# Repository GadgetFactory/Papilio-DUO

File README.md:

Papilio-DUO
==============

This is the next generation Papilio FPGA board with a Spartan6 Powered Papilio FPGA on the top and an atmega32u4 Arduino derived design on the bottom.

Features
--------
* Arduino Mega Footprint
* Spartan 6 FPGA
* SRAM 512K-2MB
* FT2232H USB
* atmega32u4 AVR

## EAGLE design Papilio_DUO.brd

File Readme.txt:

BPC3012 Papilio DUO Manufacturing Package - Current Version 1.7

Special assembly instructions:
	-Use RED for the PCB color and white for the silkscreen color.

Test Plan Home Page:
	- http://www.gadgetfactory.net/opmanuals/index.php?n=Main.PapilioDUO

CHANGELOG
2/11/2015 V1.7
	-Added a 2MB and 512KB marking to the top silkscreen.

1/7/2015 V1.6
	-Made the through holes for mounting on the micro-usb via's instead of holes so they can be soldered.
	-Removed Kickstarter edition
	-Fixed angles on some of the traces
	-PCB color is RED now.

9/30/2014 V1.5 - Kickstarter Edition
	-Added TQFP footprint for the ATmega32U4
	-Changed values for LED resistors so they won't be so bright. R7, R29, R30
	-Changed size of the EEPROM used by the FT2232H chip from 1K to 2K. This allows us to look like official Xilinx Cable. U3
	-Fixed up some silkscreen markings to make it more obvious how to place the parts.
	-Added the Kickstarter Special Edition Marking
	-Changed PCB color to Black

7/30/2014 V1.4
	-Added getting started URL
	-Fixed full silkscreen	

6/4/2014 V1.4
	-Fixed the mounting holes
	-Removed original Arduino mounting holes

4/16/2014 V1.3
	-VBUS connected
	-RX/TX LED's changed to port B
	-Silkscreen changes
	-HDMI removed

3/5/2014 V1.2
	-Shrunk the board to 100cm in order to better fit Chinese standards and save money in manufacturing.

3/5/2014 V1.1
	-Fixed problems for manufacturability (thanks to Mitch at Hackvana)
		-Fixed clearance problem on FPGA pins 144 and 36
		-Moved trace between FT2232H pins 10 and 11 to inside of part so it does not look like a solder bridge up on inspection.
		-Fixed Silkscreen size for the 22-53 numbering
		-Updated the CC-BY-SA text to indicate license number CC-BY-SA 4.0

3/3/2014 V1.0
	Initial Release

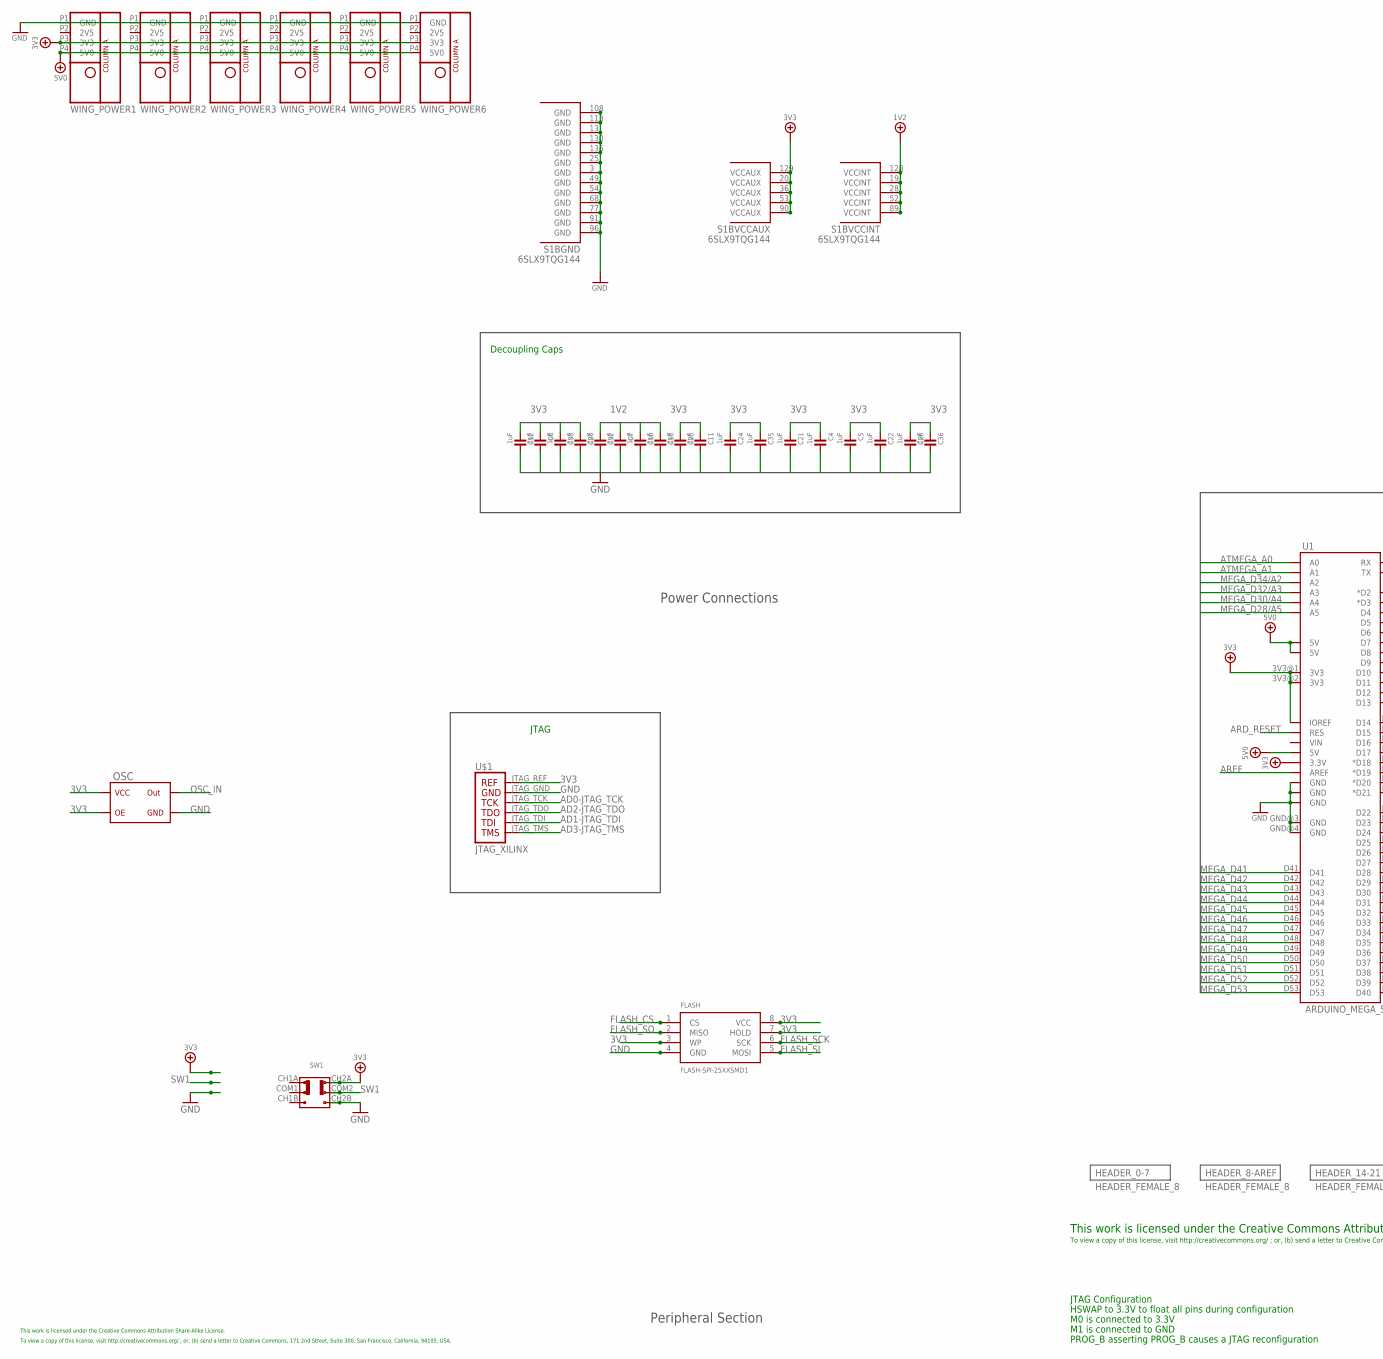
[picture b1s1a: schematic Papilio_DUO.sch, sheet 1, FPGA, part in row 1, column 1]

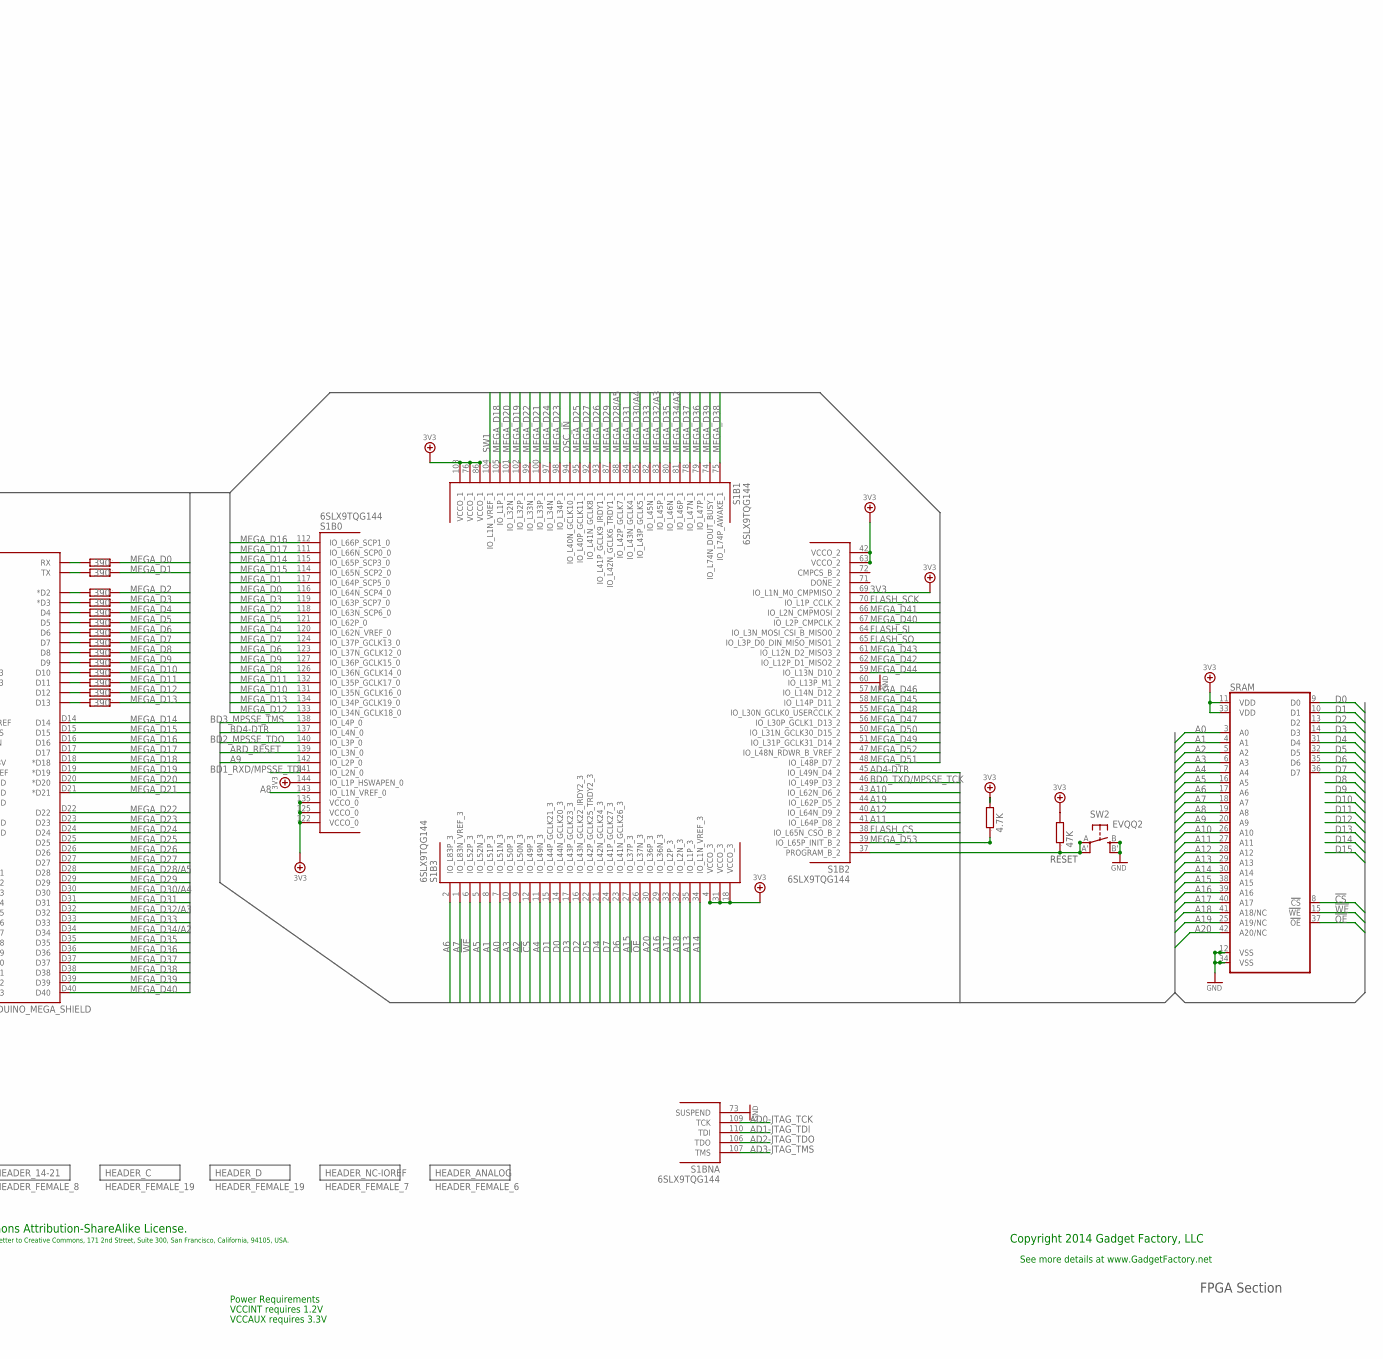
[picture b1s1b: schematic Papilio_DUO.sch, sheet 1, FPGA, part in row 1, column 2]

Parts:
C4, C5, C6, C7, C10, C11, C12, C13, C21, C22, C23, C24, C25, C26, C32, C33, C35, C36: .1uF; 0603; PARTNO GRM188F51E104ZA01D
FLASH: FLASH-SPI-25XXSMD1; SO08-EIAJ; PARTNO MX25L6445EM2I-10G
OSC: OSC1; PARTNO ASV-32.000MHZ-E-T
R8, R9, R10, R11, R12, R13, R14, R15, R16, R17, R18, R19, R20, R21: 390; 0603; PARTNO RMCF0603JT390R
R31: 47K; 0805; PARTNO RMCF0805JT47K0
R32: 4.7K; 0603; PARTNO RMCF0603JT4K70
S1: 6SLX9TQG144; TQ144; PARTNO XC6SLX9-2TQG144C
SRAM: ISSI_SRAM_8BIT; TSOP44-II; PARTNO IS61WV20488BLL-10TLI
SW1: SWITCH-2CH-6P-3010010P1; 6P-2CH-2.54-9.1X3.5X3.2+2H; PARTNO EG1271
SW2: EVQQ2; EVQ-Q2; PARTNO PTS525SM10SMTR LFS
U1: ARDUINO_MEGA_SHIELD
U$1: JTAG_XILINX; JTAG
WING_POWER1, WING_POWER2, WING_POWER3, WING_POWER4, WING_POWER5, WING_POWER6: HEADER_FEMALE_4; POWER_NO_TEXT; PARTNO PPTC041LFBN-RC

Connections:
1V2: C7.1, C10.1, C13.1, C32.1, S1.19 (VCCINT), S1.28 (VCCINT), S1.52 (VCCINT), S1.89 (VCCINT), S1.128 (VCCINT); also elsewhere on the board
3V3: C4.1, C5.1, C6.1, C11.1, C12.1, C21.1, C22.1, C23.1, C24.1, C25.1, C26.1, C33.1, C35.1, C36.1, FLASH.3 (WP), FLASH.7 (HOLD), FLASH.8 (VCC), OSC.1@1 (OE), OSC.4@4 (VCC), R31.2, R32.2, S1.4 (VCCO_3), S1.18 (VCCO_3), S1.20 (VCCAUX), S1.31 (VCCO_3), S1.36 (VCCAUX), S1.42 (VCCO_2), S1.53 (VCCAUX), S1.63 (VCCO_2), S1.69 (IO_L1N_M0_CMPMISO_2), S1.76 (VCCO_1), S1.86 (VCCO_1), S1.90 (VCCAUX), S1.103 (VCCO_1), S1.122 (VCCO_0), S1.125 (VCCO_0), S1.129 (VCCAUX), S1.135 (VCCO_0), S1.144 (IO_L1P_HSWAPEN_0), SRAM.11 (VDD), SRAM.33 (VDD), SW1.CH2A, U1.3.3V, U1.3V3@1 (3V3), U1.3V3@2 (3V3), U1.IOREF, U$1.JTAG_REF, WING_POWER1.P3 (3V3), WING_POWER2.P3 (3V3), WING_POWER3.P3 (3V3), WING_POWER4.P3 (3V3), WING_POWER5.P3 (3V3), WING_POWER6.P3 (3V3); also elsewhere on the board
5V0: U1.5V@0 (5V), U1.5V@1 (5V), U1.5V@2 (5V), WING_POWER1.P4 (5V0), WING_POWER2.P4 (5V0), WING_POWER3.P4 (5V0), WING_POWER4.P4 (5V0), WING_POWER5.P4 (5V0), WING_POWER6.P4 (5V0); also elsewhere on the board
!CS: S1.12 (IO_L49P_3), SRAM.8 (!CS)
!OE: S1.26 (IO_L37N_3), SRAM.37 (!OE)
!WE: S1.6 (IO_L52P_3), SRAM.15 (!WE)
A0: S1.7 (IO_L51N_3), SRAM.3 (A0)
A1: S1.8 (IO_L51P_3), SRAM.4 (A1)
A2: S1.9 (IO_L50N_3), SRAM.5 (A2)
A3: S1.10 (IO_L50P_3), SRAM.6 (A3)
A4: S1.11 (IO_L49N_3), SRAM.7 (A4)
A5: S1.5 (IO_L52N_3), SRAM.16 (A5)
A6: S1.2 (IO_L83P_3), SRAM.17 (A6)
A7: S1.1 (IO_L83N_VREF_3), SRAM.18 (A7)
A8: S1.143 (IO_L1N_VREF_0), SRAM.19 (A8)
A9: S1.142 (IO_L2P_0), SRAM.20 (A9)
A10: S1.43 (IO_L62N_D6_2), SRAM.26 (A10)
A11: S1.41 (IO_L64P_D8_2), SRAM.27 (A11)
A12: S1.40 (IO_L64N_D9_2), SRAM.28 (A12)
A13: S1.35 (IO_L1P_3), SRAM.29 (A13)
A14: S1.34 (IO_L1N_VREF_3), SRAM.30 (A14)
A15: S1.27 (IO_L37P_3), SRAM.38 (A15)
A16: S1.29 (IO_L36N_3), SRAM.39 (A16)
A17: S1.33 (IO_L2P_3), SRAM.40 (A17)
A18: S1.32 (IO_L2N_3), SRAM.41 (A18/NC)
A19: S1.44 (IO_L62P_D5_2), SRAM.25 (A19/NC)
A20: S1.30 (IO_L36P_3), SRAM.42 (A20/NC)
AD0-JTAG_TCK: S1.109 (TCK), U$1.JTAG_TCK; also elsewhere on the board
AD1-JTAG_TDI: S1.110 (TDI), U$1.JTAG_TDI; also elsewhere on the board
AD2-JTAG_TDO: S1.106 (TDO), U$1.JTAG_TDO; also elsewhere on the board
AD3-JTAG_TMS: S1.107 (TMS), U$1.JTAG_TMS; also elsewhere on the board
AD4-DTR: S1.45 (IO_L49N_D4_2); also elsewhere on the board
ARD_RESET: S1.139 (IO_L3N_0), U1.RES; also elsewhere on the board
AREF: U1.AREF; also elsewhere on the board
ATMEGA_A0: U1.A0; also elsewhere on the board
ATMEGA_A1: U1.A1; also elsewhere on the board
ATMEGA_D0/RX: R21.2, U1.RX; also elsewhere on the board
ATMEGA_D1/TX: R20.2, U1.TX; also elsewhere on the board
ATMEGA_D2: R19.2, U1.D2 (*D2); also elsewhere on the board
ATMEGA_D3: R18.2, U1.D3 (*D3); also elsewhere on the board
ATMEGA_D4: R17.2, U1.D4; also elsewhere on the board
ATMEGA_D5*: R16.2, U1.D5; also elsewhere on the board
ATMEGA_D6*: R15.2, U1.D6; also elsewhere on the board
ATMEGA_D7: R14.2, U1.D7; also elsewhere on the board
ATMEGA_IO8: R13.2, U1.D8; also elsewhere on the board
ATMEGA_IO9*: R12.2, U1.D9; also elsewhere on the board
ATMEGA_IO10*: R11.2, U1.D10; also elsewhere on the board
ATMEGA_IO11*: R10.2, U1.D11; also elsewhere on the board
ATMEGA_IO12: R9.2, U1.D12; also elsewhere on the board
ATMEGA_IO13*: R8.2, U1.D13; also elsewhere on the board
BD0_TXD/MPSSE_TCK: S1.46 (IO_L49P_D3_2); also elsewhere on the board
BD1_RXD/MPSSE_TDI: S1.141 (IO_L2N_0); also elsewhere on the board
BD2_MPSSE_TDO: S1.140 (IO_L3P_0); also elsewhere on the board
BD3_MPSSE_TMS: S1.138 (IO_L4P_0); also elsewhere on the board
BD4-DTR: S1.137 (IO_L4N_0); also elsewhere on the board
D0: S1.14 (IO_L44N_GCLK20_3), SRAM.9 (D0)
D1: S1.15 (IO_L44P_GCLK21_3), SRAM.10 (D1)
D2: S1.16 (IO_L43N_GCLK22_IRDY2_3), SRAM.13 (D2)
D3: S1.17 (IO_L43P_GCLK23_3), SRAM.14 (D3)
D4: S1.21 (IO_L42N_GCLK24_3), SRAM.31 (D4)
D5: S1.22 (IO_L42P_GCLK25_TRDY2_3), SRAM.32 (D5)
D6: S1.23 (IO_L41N_GCLK26_3), SRAM.35 (D6)
D7: S1.24 (IO_L41P_GCLK27_3), SRAM.36 (D7)
FLASH_CS: FLASH.1 (CS), S1.38 (IO_L65N_CSO_B_2)
FLASH_SCK: FLASH.6 (SCK), S1.70 (IO_L1P_CCLK_2)
FLASH_SI: FLASH.5 (MOSI), S1.64 (IO_L3N_MOSI_CSI_B_MISO0_2)
FLASH_SO: FLASH.2 (MISO), S1.65 (IO_L3P_D0_DIN_MISO_MISO1_2)
GND: C4.2, C5.2, C6.2, C7.2, C10.2, C11.2, C12.2, C13.2, C21.2, C22.2, C23.2, C24.2, C25.2, C26.2, C32.2, C33.2, C35.2, C36.2, FLASH.4 (GND), OSC.2@2 (GND), S1.3 (GND), S1.13 (GND), S1.25 (GND), S1.49 (GND), S1.54 (GND), S1.60 (IO_L13P_M1_2), S1.68 (GND), S1.73 (SUSPEND), S1.77 (GND), S1.91 (GND), S1.96 (GND), S1.108 (GND), S1.113 (GND), S1.130 (GND), S1.136 (GND), SRAM.12 (VSS), SRAM.34 (VSS), SW1.CH2B, SW2.B (S), SW2.B' (S1), U1.GND@0 (GND), U1.GND@1 (GND), U1.GND@2 (GND), U1.GND@3 (GND), U1.GND@4 (GND), U$1.JTAG_GND, WING_POWER1.P1 (GND), WING_POWER2.P1 (GND), WING_POWER3.P1 (GND), WING_POWER4.P1 (GND), WING_POWER5.P1 (GND), WING_POWER6.P1 (GND); also elsewhere on the board
MEGA_D0: R21.1, S1.116 (IO_L64N_SCP4_0)
MEGA_D1: R20.1, S1.117 (IO_L64P_SCP5_0)
MEGA_D2: R19.1, S1.118 (IO_L63N_SCP6_0)
MEGA_D3: R18.1, S1.119 (IO_L63P_SCP7_0)
MEGA_D4: R17.1, S1.120 (IO_L62N_VREF_0)
MEGA_D5: R16.1, S1.121 (IO_L62P_0)
MEGA_D6: R15.1, S1.123 (IO_L37N_GCLK12_0)
MEGA_D7: R14.1, S1.124 (IO_L37P_GCLK13_0)
MEGA_D8: R13.1, S1.126 (IO_L36N_GCLK14_0)
MEGA_D9: R12.1, S1.127 (IO_L36P_GCLK15_0)
MEGA_D10: R11.1, S1.131 (IO_L35N_GCLK16_0)
MEGA_D11: R10.1, S1.132 (IO_L35P_GCLK17_0)
MEGA_D12: R9.1, S1.133 (IO_L34N_GCLK18_0)
MEGA_D13: R8.1, S1.134 (IO_L34P_GCLK19_0)
MEGA_D14: S1.115 (IO_L65P_SCP3_0), U1.D14; also elsewhere on the board
MEGA_D15: S1.114 (IO_L65N_SCP2_0), U1.D15; also elsewhere on the board
MEGA_D16: S1.112 (IO_L66P_SCP1_0), U1.D16; also elsewhere on the board
MEGA_D17: S1.111 (IO_L66N_SCP0_0), U1.D17
MEGA_D18: S1.105 (IO_L1P_1), U1.D18 (*D18)
MEGA_D19: S1.102 (IO_L32P_1), U1.D19 (*D19)
MEGA_D20: S1.101 (IO_L32N_1), U1.D20 (*D20)
MEGA_D21: S1.100 (IO_L33P_1), U1.D21 (*D21)
MEGA_D22: S1.99 (IO_L33N_1), U1.D22
MEGA_D23: S1.98 (IO_L34P_1), U1.D23
MEGA_D24: S1.97 (IO_L34N_1), U1.D24
MEGA_D25: S1.95 (IO_L40P_GCLK11_1), U1.D25
MEGA_D26: S1.93 (IO_L41P_GCLK9_IRDY1_1), U1.D26
MEGA_D27: S1.92 (IO_L41N_GCLK8_1), U1.D27
MEGA_D28/A5: S1.88 (IO_L42P_GCLK7_1), U1.A5, U1.D28; also elsewhere on the board
MEGA_D29: S1.87 (IO_L42N_GCLK6_TRDY1_1), U1.D29
MEGA_D30/A4: S1.85 (IO_L43P_GCLK5_1), U1.A4, U1.D30; also elsewhere on the board
MEGA_D31: S1.84 (IO_L43N_GCLK4_1), U1.D31
MEGA_D32/A3: S1.83 (IO_L45P_1), U1.A3, U1.D32; also elsewhere on the board
MEGA_D33: S1.82 (IO_L45N_1), U1.D33
MEGA_D34/A2: S1.81 (IO_L46P_1), U1.A2, U1.D34; also elsewhere on the board
MEGA_D35: S1.80 (IO_L46N_1), U1.D35
MEGA_D36: S1.79 (IO_L47P_1), U1.D36
MEGA_D37: S1.78 (IO_L47N_1), U1.D37
MEGA_D38: S1.75 (IO_L74P_AWAKE_1), U1.D38
MEGA_D39: S1.74 (IO_L74N_DOUT_BUSY_1), U1.D39
MEGA_D40: S1.67 (IO_L2P_CMPCLK_2), U1.D40
MEGA_D41: S1.66 (IO_L2N_CMPMOSI_2), U1.D41
MEGA_D42: S1.62 (IO_L12P_D1_MISO2_2), U1.D42
MEGA_D43: S1.61 (IO_L12N_D2_MISO3_2), U1.D43
MEGA_D44: S1.59 (IO_L13N_D10_2), U1.D44
MEGA_D45: S1.58 (IO_L14P_D11_2), U1.D45
MEGA_D46: S1.57 (IO_L14N_D12_2), U1.D46
MEGA_D47: S1.56 (IO_L30P_GCLK1_D13_2), U1.D47
MEGA_D48: S1.55 (IO_L30N_GCLK0_USERCCLK_2), U1.D48
MEGA_D49: S1.51 (IO_L31P_GCLK31_D14_2), U1.D49
MEGA_D50: S1.50 (IO_L31N_GCLK30_D15_2), U1.D50
MEGA_D51: S1.48 (IO_L48P_D7_2), U1.D51
MEGA_D52: S1.47 (IO_L48N_RDWR_B_VREF_2), U1.D52
MEGA_D53: R32.1, S1.39 (IO_L65P_INIT_B_2), U1.D53
OSC_IN: OSC.3@3 (OUT), S1.94 (IO_L40N_GCLK10_1)
RESET: R31.1, S1.37 (PROGRAM_B_2), SW2.A, SW2.A' (P1)
SW1: S1.104 (IO_L1N_VREF_1), SW1.COM2

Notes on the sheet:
JTAG Configuration
HSWAP to 3.3V to float all pins during configuration
M0 is connected to 3.3V
M1 is connected to GND
PROG_B asserting PROG_B causes a JTAG reconfiguration
Power Requirements
VCCINT requires 1.2V
VCCAUX requires 3.3V
Decoupling Caps
JTAG
Copyright 2014 Gadget Factory, LLC
This work is licensed under the Creative Commons Attribution-ShareAlike License.
To view a copy of this license, visit http://creativecommons.org/ ; or, (b) send a letter to Creative Commons, 171 2nd Street, Suite 300, San Francisco, California, 94105, USA.
See more details at www.GadgetFactory.net
This work is licensed under the Creative Commons Attribution Share-Alike License.
Power Connections
Peripheral Section
FPGA Section
RESET

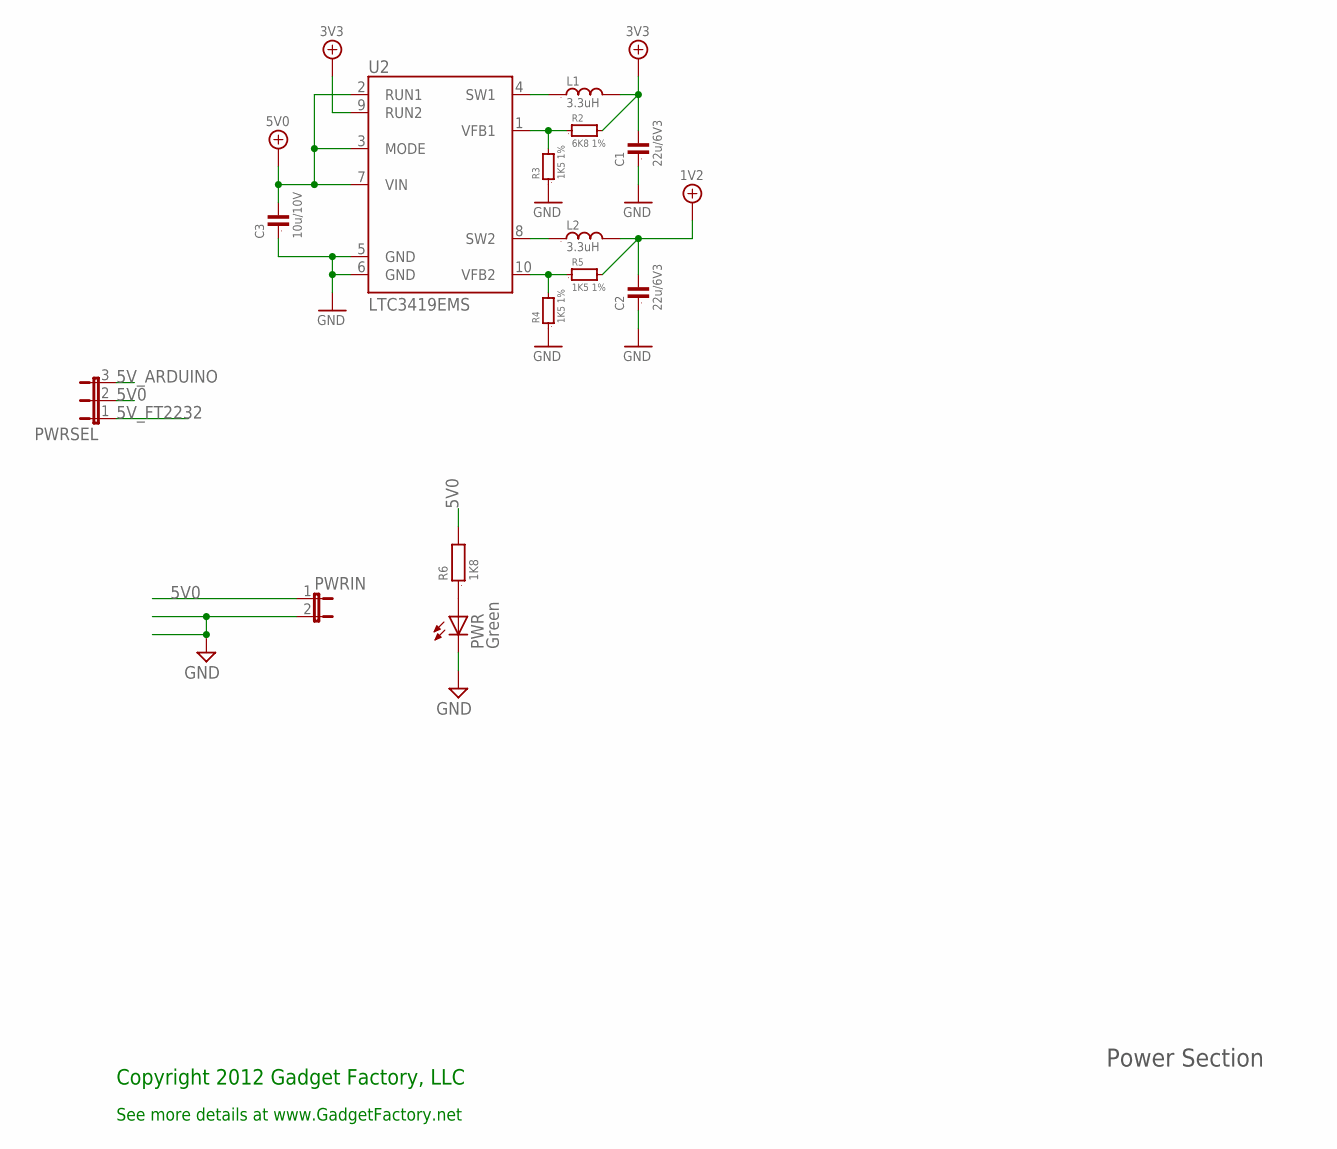
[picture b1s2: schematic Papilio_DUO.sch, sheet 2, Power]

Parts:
C1, C2: 22u/6V3; 0805; PARTNO GRM21BR60J226ME39L
C3: 10u/10V; 0805; PARTNO C0805C106K9PACTU
L1, L2: 3.3uH; VLS3015; PARTNO VLS3015T-3R3M1R2
PWR: Green; CHIP-LED0805; PARTNO LTST-C171EKT
PWRIN: JP1E; JP1; PARTNO 68000-102HLF
PWRSEL: JP2E; JP2; PARTNO 68000-103HLF
R2: 6K8 1%; 0603; PARTNO CRCW06036K80FKEA
R3, R4, R5: 1K5 1%; 0603; PARTNO CRCW06031K50FKEA
R6: 1K8; 0603; PARTNO RMCF0603JT1K80
U2: LTC3419EMS; MSOP10; PARTNO LTC3419EMS#PBF

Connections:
1V2: C2.2, L2.2, R5.2; also elsewhere on the board
3V3: C1.2, L1.2, R2.2, U2.9 (RUN2); also elsewhere on the board
5V0: C3.2, PWRIN.1, PWRSEL.2, R6.2, U2.2 (RUN1), U2.3 (MODE), U2.7 (VIN); also elsewhere on the board
5V_ARDUINO: PWRSEL.3; also elsewhere on the board
5V_FT2232: PWRSEL.1; also elsewhere on the board
FB_1V2: R4.2, R5.1, U2.10 (VFB2)
FB_3V3: R2.1, R3.2, U2.1 (VFB1)
GND: C1.1, C2.1, C3.1, PWR.C, PWRIN.2, R3.1, R4.1, U2.5 (GND), U2.6 (GND); also elsewhere on the board
unnamed: PWR.A, R6.1
SW_1V2: L2.1, U2.8 (SW2)
SW_3V3: L1.1, U2.4 (SW1)

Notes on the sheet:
Power Section
Copyright 2012 Gadget Factory, LLC
See more details at www.GadgetFactory.net

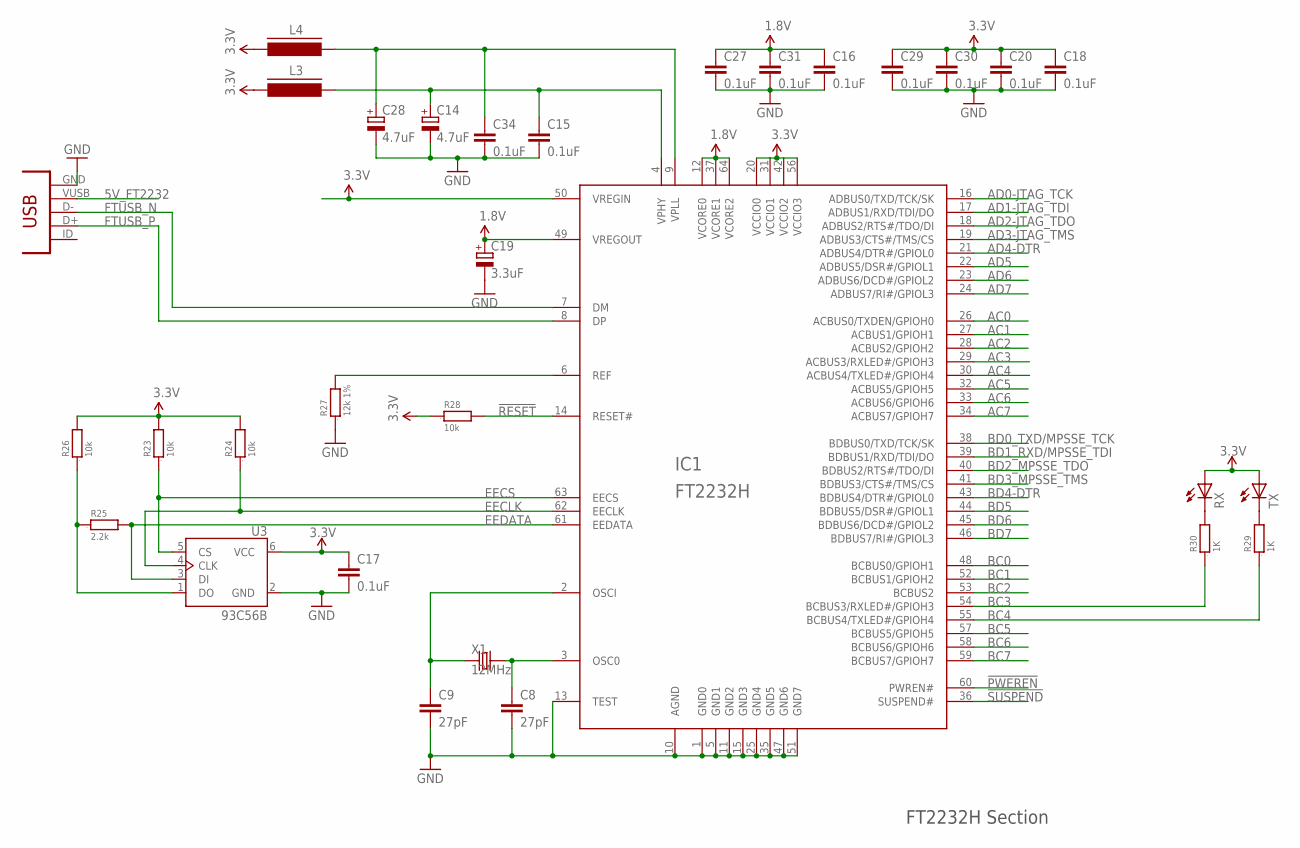
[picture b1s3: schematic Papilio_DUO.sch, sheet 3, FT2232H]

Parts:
C8, C9: 27pF; C603; PARTNO CL10C270JB8NNNC
C14, C28: 4.7uF; SMC_A; PARTNO T491A475M010AT
C15, C16, C17, C18, C20, C27, C29, C30, C31, C34: 0.1uF; C603; PARTNO GRM188F51E104ZA01D
C19: 3.3uF; SMC_A; PARTNO T491A335K016AT7280
FPGAUSB: CONN_USB; CONN_USB_MINI-B; PARTNO USB-M26FTR
IC1: FT2232H; LQFP64; PARTNO FT2232HL-REEL
L3, L4: FERRITE_BEAD603; FB603; PARTNO MMZ1608R600A
R23, R24, R26, R28: 10k; 0603; PARTNO RMCF0603JT10K0
R25: 2.2k; 0603; PARTNO RMCF0603JT2K20
R27: 12k 1%; 0603; PARTNO RMCF0603FT12K0
R29, R30: 1K; 0603; PARTNO RMCF0603JT470R
RX: LEDCHIP-LED0805; CHIP-LED0805; PARTNO LTST-C170KGKT
TX: LEDCHIP-LED0805; CHIP-LED0805; PARTNO LTST-C170KGKT
U3: 93C56B; SOT23-6; PARTNO 93C46BT-I/OT
X1: 12MHz; 4X6; PARTNO ABM7-12.000MHZ-D2Y-T

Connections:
1.8V: C16.1, C19.+, C27.1, C31.1, IC1.12 (VCORE0), IC1.37 (VCORE1), IC1.49 (VREGOUT), IC1.64 (VCORE2)
3V3: C17.1, C18.1, C20.1, C29.1, C30.1, IC1.20 (VCCIO0), IC1.31 (VCCIO1), IC1.42 (VCCIO2), IC1.50 (VREGIN), IC1.56 (VCCIO3), L3.2, L4.2, R23.2, R24.2, R26.2, R28.1, RX.A, TX.A, U3.6 (VCC); also elsewhere on the board
5V_FT2232: FPGAUSB.VUSB; also elsewhere on the board
!PWEREN: IC1.60 (PWREN#)
!RESET: IC1.14 (RESET#), R28.2
!SUSPEND: IC1.36 (SUSPEND#)
AC0: IC1.26 (ACBUS0/TXDEN/GPIOH0)
AC1: IC1.27 (ACBUS1/GPIOH1)
AC2: IC1.28 (ACBUS2/GPIOH2)
AC3: IC1.29 (ACBUS3/RXLED#/GPIOH3)
AC4: IC1.30 (ACBUS4/TXLED#/GPIOH4)
AC5: IC1.32 (ACBUS5/GPIOH5)
AC6: IC1.33 (ACBUS6/GPIOH6)
AC7: IC1.34 (ACBUS7/GPIOH7)
AD0-JTAG_TCK: IC1.16 (ADBUS0/TXD/TCK/SK); also elsewhere on the board
AD1-JTAG_TDI: IC1.17 (ADBUS1/RXD/TDI/DO); also elsewhere on the board
AD2-JTAG_TDO: IC1.18 (ADBUS2/RTS#/TDO/DI); also elsewhere on the board
AD3-JTAG_TMS: IC1.19 (ADBUS3/CTS#/TMS/CS); also elsewhere on the board
AD4-DTR: IC1.21 (ADBUS4/DTR#/GPIOL0); also elsewhere on the board
AD5: IC1.22 (ADBUS5/DSR#/GPIOL1)
AD6: IC1.23 (ADBUS6/DCD#/GPIOL2)
AD7: IC1.24 (ADBUS7/RI#/GPIOL3)
BC0: IC1.48 (BCBUS0/GPIOH1)
BC1: IC1.52 (BCBUS1/GPIOH2)
BC2: IC1.53 (BCBUS2)
BC3: IC1.54 (BCBUS3/RXLED#/GPIOH3), R30.1
BC4: IC1.55 (BCBUS4/TXLED#/GPIOH4), R29.1
BC5: IC1.57 (BCBUS5/GPIOH5)
BC6: IC1.58 (BCBUS6/GPIOH6)
BC7: IC1.59 (BCBUS7/GPIOH7)
BD0_TXD/MPSSE_TCK: IC1.38 (BDBUS0/TXD/TCK/SK); also elsewhere on the board
BD1_RXD/MPSSE_TDI: IC1.39 (BDBUS1/RXD/TDI/DO); also elsewhere on the board
BD2_MPSSE_TDO: IC1.40 (BDBUS2/RTS#/TDO/DI); also elsewhere on the board
BD3_MPSSE_TMS: IC1.41 (BDBUS3/CTS#/TMS/CS); also elsewhere on the board
BD4-DTR: IC1.43 (BDBUS4/DTR#/GPIOL0); also elsewhere on the board
BD5: IC1.44 (BDBUS5/DSR#/GPIOL1)
BD6: IC1.45 (BDBUS6/DCD#/GPIOL2)
BD7: IC1.46 (BDBUS7/RI#/GPIOL3)
EECLK: IC1.62 (EECLK), R24.1, U3.4 (CLK)
EECS: IC1.63 (EECS), R23.1, U3.5 (CS)
EEDATA: IC1.61 (EEDATA), R25.2, U3.3 (DI)
FTUSB_N: FPGAUSB.D-, IC1.7 (DM)
FTUSB_P: FPGAUSB.D+, IC1.8 (DP)
GND: C8.2, C9.2, C14.-, C15.2, C16.2, C17.2, C18.2, C19.-, C20.2, C27.2, C28.-, C29.2, C30.2, C31.2, C34.2, FPGAUSB.GND, IC1.1 (GND0), IC1.5 (GND1), IC1.10 (AGND), IC1.11 (GND2), IC1.13 (TEST), IC1.15 (GND3), IC1.25 (GND4), IC1.35 (GND5), IC1.47 (GND6), IC1.51 (GND7), R27.1, U3.2 (GND); also elsewhere on the board
unnamed: IC1.6 (REF), R27.2
unnamed: C9.1, IC1.2 (OSCI), X1.1 (X1)
unnamed: C8.1, IC1.3 (OSC0), X1.2 (X2)
unnamed: R30.2, RX.C
unnamed: R29.2, TX.C
unnamed: R25.1, R26.1, U3.1 (DO)
unnamed: C14.+, C15.1, IC1.4 (VPHY), L3.1
unnamed: C28.+, C34.1, IC1.9 (VPLL), L4.1

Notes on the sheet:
FT2232H Section

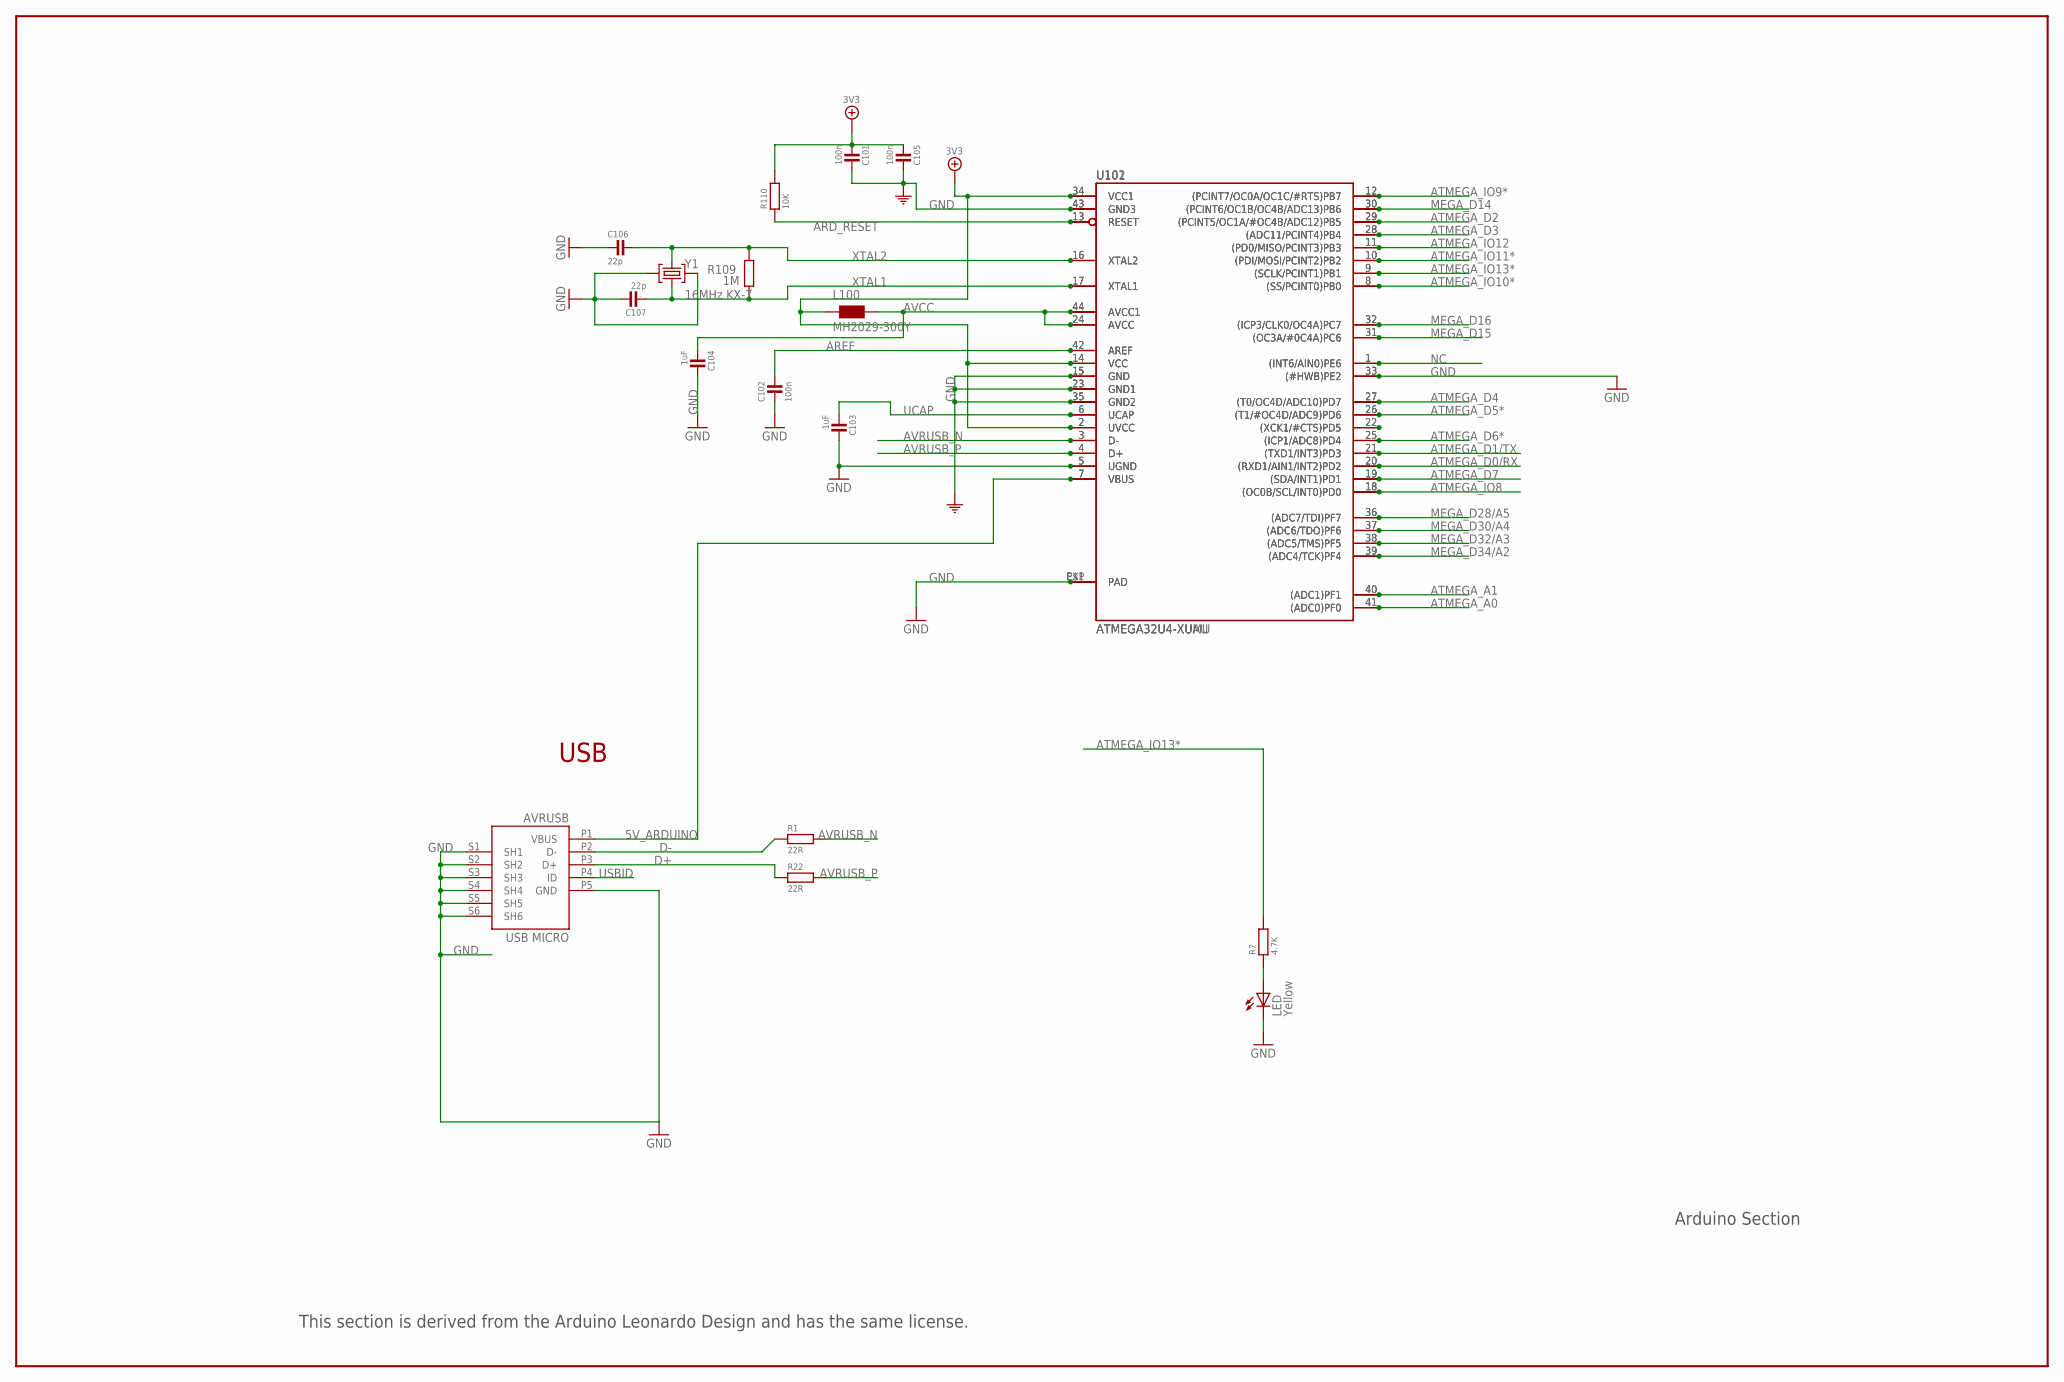
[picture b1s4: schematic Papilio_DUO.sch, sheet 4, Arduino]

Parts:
AVRUSB: USB MICRO; CON2_USB_MICRO_B_AT; PARTNO 10118193-0001LF
C101, C102, C105: 100n; 0603; PARTNO GRM188F51E104ZA01D
C103, C104: 1uF; 0603; PARTNO C1608X5R1A105K080AC
C106, C107: 22p; 0603; PARTNO C1608C0G1H220J080AA
L100: MH2029-300Y; 0805; PARTNO MH2029-300YCT-ND
LED: Yellow; CHIP-LED0805; PARTNO LTST-C170KGKT
R1, R22: 22R; 0805; PARTNO RMCF0805JT22R0
R7: 4.7K; 0603; PARTNO RMCF0603JT1K00
R109: 1M; 0603; PARTNO RMCF0603JT1M00
R110: 10K; 0603; PARTNO RMCF0603JT10K0
U101: ATMEGA32U4-XUMU; QFN44ML7X7; PARTNO ATMEGA32U4RC-MUR
U102: ATMEGA32U4-XUAU; TQFP44-PAD
Y1: 16MHz KX-7; CRYSTAL-3.2-2.5; PARTNO ABM8G-16.000MHZ-B4Y-T

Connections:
3V3: C101.1, C105.1, L100.1, R110.2, U101.2 (UVCC), U101.14 (VCC), U101.34 (VCC1), U102.2 (UVCC), U102.14 (VCC), U102.34 (VCC1); also elsewhere on the board
5V_ARDUINO: AVRUSB.P1 (VBUS), U101.7 (VBUS), U102.7 (VBUS); also elsewhere on the board
ARD_RESET: R110.1, U101.13 (RESET), U102.13 (RESET); also elsewhere on the board
AREF: C102.2, U101.42 (AREF), U102.42 (AREF); also elsewhere on the board
ATMEGA_A0: U101.41 ((ADC0)PF0), U102.41 ((ADC0)PF0); also elsewhere on the board
ATMEGA_A1: U101.40 ((ADC1)PF1), U102.40 ((ADC1)PF1); also elsewhere on the board
ATMEGA_D0/RX: U101.20 ((RXD1/AIN1/INT2)PD2), U102.20 ((RXD1/AIN1/INT2)PD2); also elsewhere on the board
ATMEGA_D1/TX: U101.21 ((TXD1/INT3)PD3), U102.21 ((TXD1/INT3)PD3); also elsewhere on the board
ATMEGA_D2: U101.29 ((PCINT5/OC1A/#OC4B/ADC12)PB5), U102.29 ((PCINT5/OC1A/#OC4B/ADC12)PB5); also elsewhere on the board
ATMEGA_D3: U101.28 ((ADC11/PCINT4)PB4), U102.28 ((ADC11/PCINT4)PB4); also elsewhere on the board
ATMEGA_D4: U101.27 ((T0/OC4D/ADC10)PD7), U102.27 ((T0/OC4D/ADC10)PD7); also elsewhere on the board
ATMEGA_D5*: U101.26 ((T1/#OC4D/ADC9)PD6), U102.26 ((T1/#OC4D/ADC9)PD6); also elsewhere on the board
ATMEGA_D6*: U101.25 ((ICP1/ADC8)PD4), U102.25 ((ICP1/ADC8)PD4); also elsewhere on the board
ATMEGA_D7: U101.19 ((SDA/INT1)PD1), U102.19 ((SDA/INT1)PD1); also elsewhere on the board
ATMEGA_IO8: U101.18 ((OC0B/SCL/INT0)PD0), U102.18 ((OC0B/SCL/INT0)PD0); also elsewhere on the board
ATMEGA_IO9*: U101.12 ((PCINT7/OC0A/OC1C/#RTS)PB7), U102.12 ((PCINT7/OC0A/OC1C/#RTS)PB7); also elsewhere on the board
ATMEGA_IO10*: U101.8 ((SS/PCINT0)PB0), U102.8 ((SS/PCINT0)PB0); also elsewhere on the board
ATMEGA_IO11*: U101.10 ((PDI/MOSI/PCINT2)PB2), U102.10 ((PDI/MOSI/PCINT2)PB2); also elsewhere on the board
ATMEGA_IO12: U101.11 ((PD0/MISO/PCINT3)PB3), U102.11 ((PD0/MISO/PCINT3)PB3); also elsewhere on the board
ATMEGA_IO13*: R7.2, U101.9 ((SCLK/PCINT1)PB1), U102.9 ((SCLK/PCINT1)PB1); also elsewhere on the board
AVCC: C104.1, L100.2, U101.24 (AVCC), U101.44 (AVCC1), U102.24 (AVCC), U102.44 (AVCC1)
AVRUSB_N: R1.2, U101.3 (D-), U102.3 (D-)
AVRUSB_P: R22.2, U101.4 (D+), U102.4 (D+)
D+: AVRUSB.P3 (D+), R22.1
D-: AVRUSB.P2 (D-), R1.1
GND: AVRUSB.P5 (GND), AVRUSB.S1 (SH1), AVRUSB.S2 (SH2), AVRUSB.S3 (SH3), AVRUSB.S4 (SH4), AVRUSB.S5 (SH5), AVRUSB.S6 (SH6), C101.2, C102.1, C103.2, C104.2, C105.2, C106.1, C107.2, LED.C, U101.5 (UGND), U101.15 (GND), U101.23 (GND1), U101.33 ((#HWB)PE2), U101.35 (GND2), U101.43 (GND3), U101.EXP (PAD), U102.5 (UGND), U102.15 (GND), U102.23 (GND1), U102.33 ((#HWB)PE2), U102.35 (GND2), U102.43 (GND3), U102.P$1 (PAD), Y1.2 (GND), Y1.4 (GND); also elsewhere on the board
MEGA_D14: U101.30 ((PCINT6/OC1B/OC4B/ADC13)PB6), U102.30 ((PCINT6/OC1B/OC4B/ADC13)PB6); also elsewhere on the board
MEGA_D15: U101.31 ((OC3A/#0C4A)PC6), U102.31 ((OC3A/#0C4A)PC6); also elsewhere on the board
MEGA_D16: U101.32 ((ICP3/CLK0/OC4A)PC7), U102.32 ((ICP3/CLK0/OC4A)PC7); also elsewhere on the board
MEGA_D28/A5: U101.36 ((ADC7/TDI)PF7), U102.36 ((ADC7/TDI)PF7); also elsewhere on the board
MEGA_D30/A4: U101.37 ((ADC6/TDO)PF6), U102.37 ((ADC6/TDO)PF6); also elsewhere on the board
MEGA_D32/A3: U101.38 ((ADC5/TMS)PF5), U102.38 ((ADC5/TMS)PF5); also elsewhere on the board
MEGA_D34/A2: U101.39 ((ADC4/TCK)PF4), U102.39 ((ADC4/TCK)PF4); also elsewhere on the board
unnamed: U101.22 ((XCK1/#CTS)PD5), U102.22 ((XCK1/#CTS)PD5)
unnamed: LED.A, R7.1
NC: U101.1 ((INT6/AIN0)PE6), U102.1 ((INT6/AIN0)PE6)
UCAP: C103.1, U101.6 (UCAP), U102.6 (UCAP)
USBID: AVRUSB.P4 (ID)
XTAL1: C107.1, R109.1, U101.17 (XTAL1), U102.17 (XTAL1), Y1.1 (C1)
XTAL2: C106.2, R109.2, U101.16 (XTAL2), U102.16 (XTAL2), Y1.3 (C2)

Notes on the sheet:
USB
Arduino Section
This section is derived from the Arduino Leonardo Design and has the same license.

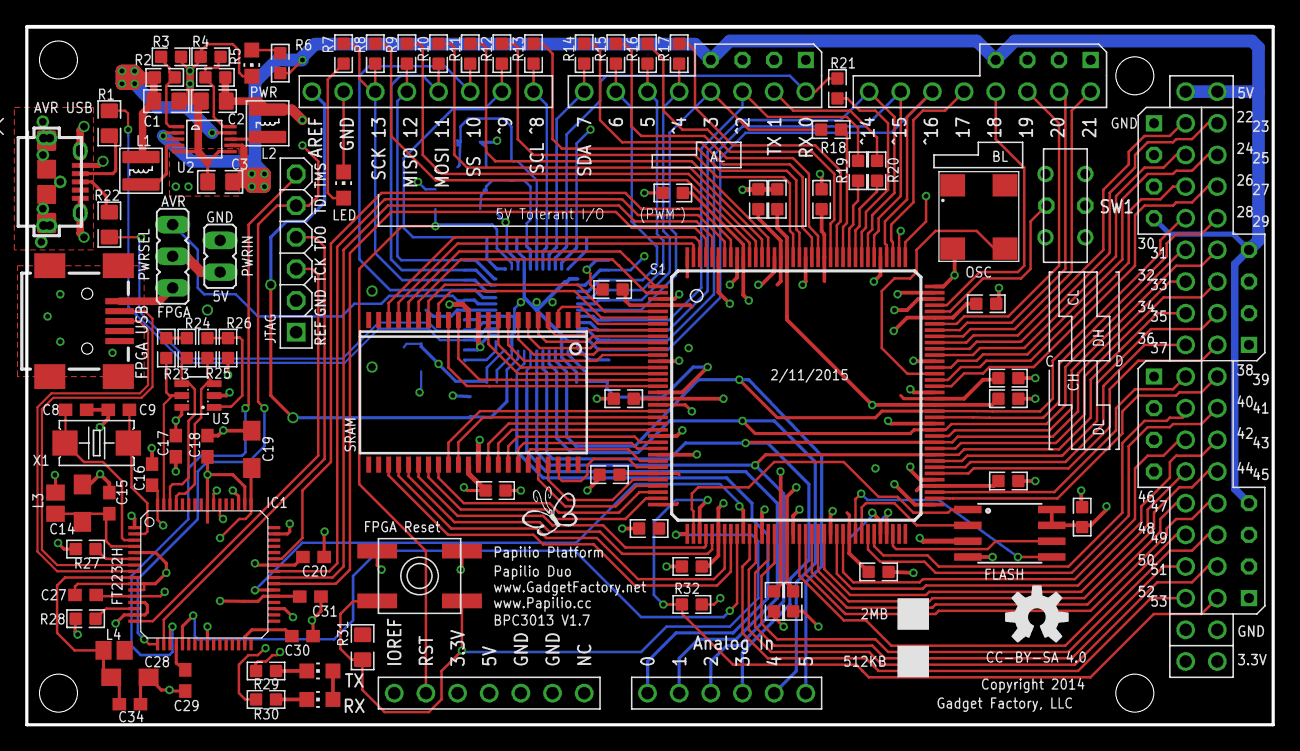
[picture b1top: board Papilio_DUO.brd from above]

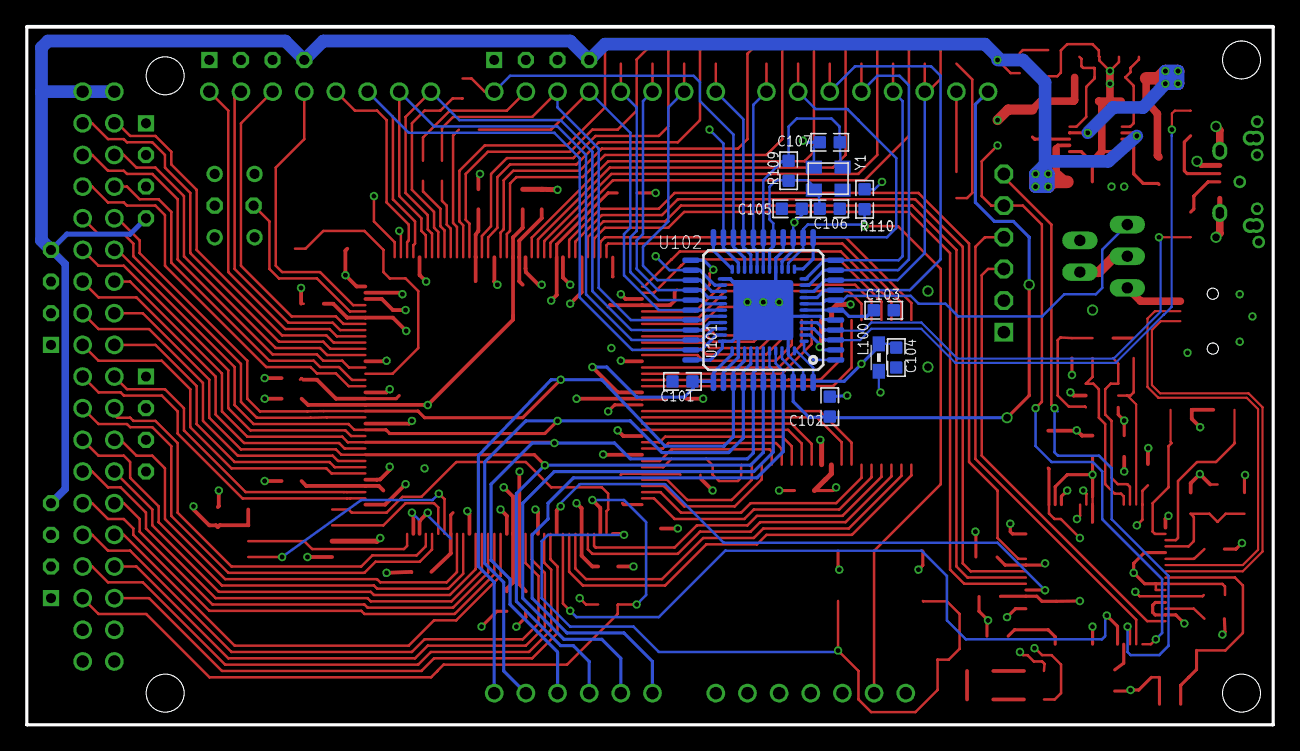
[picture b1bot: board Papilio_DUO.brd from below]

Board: 4 copper layers, 100.0 x 56.0 mm, 117 parts (13 on the bottom side), 160 nets.

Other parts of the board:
U$2, U$3, U$4, U$5: STAND-OFF-TIGHT
U$7: GADGETFACTORY_LOGO
U$9: OSHW-LOGO-M

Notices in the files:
parts and their libraries:
SparkFun-Aesthetics: Licensing: CC v3.0 Share-Alike You are welcome to use this library for commercial purposes.
bom: Copyright (C) 2010, Bob Starr
